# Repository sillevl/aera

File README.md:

# aera
Solar Powered Airquality Station using LoRaWAN

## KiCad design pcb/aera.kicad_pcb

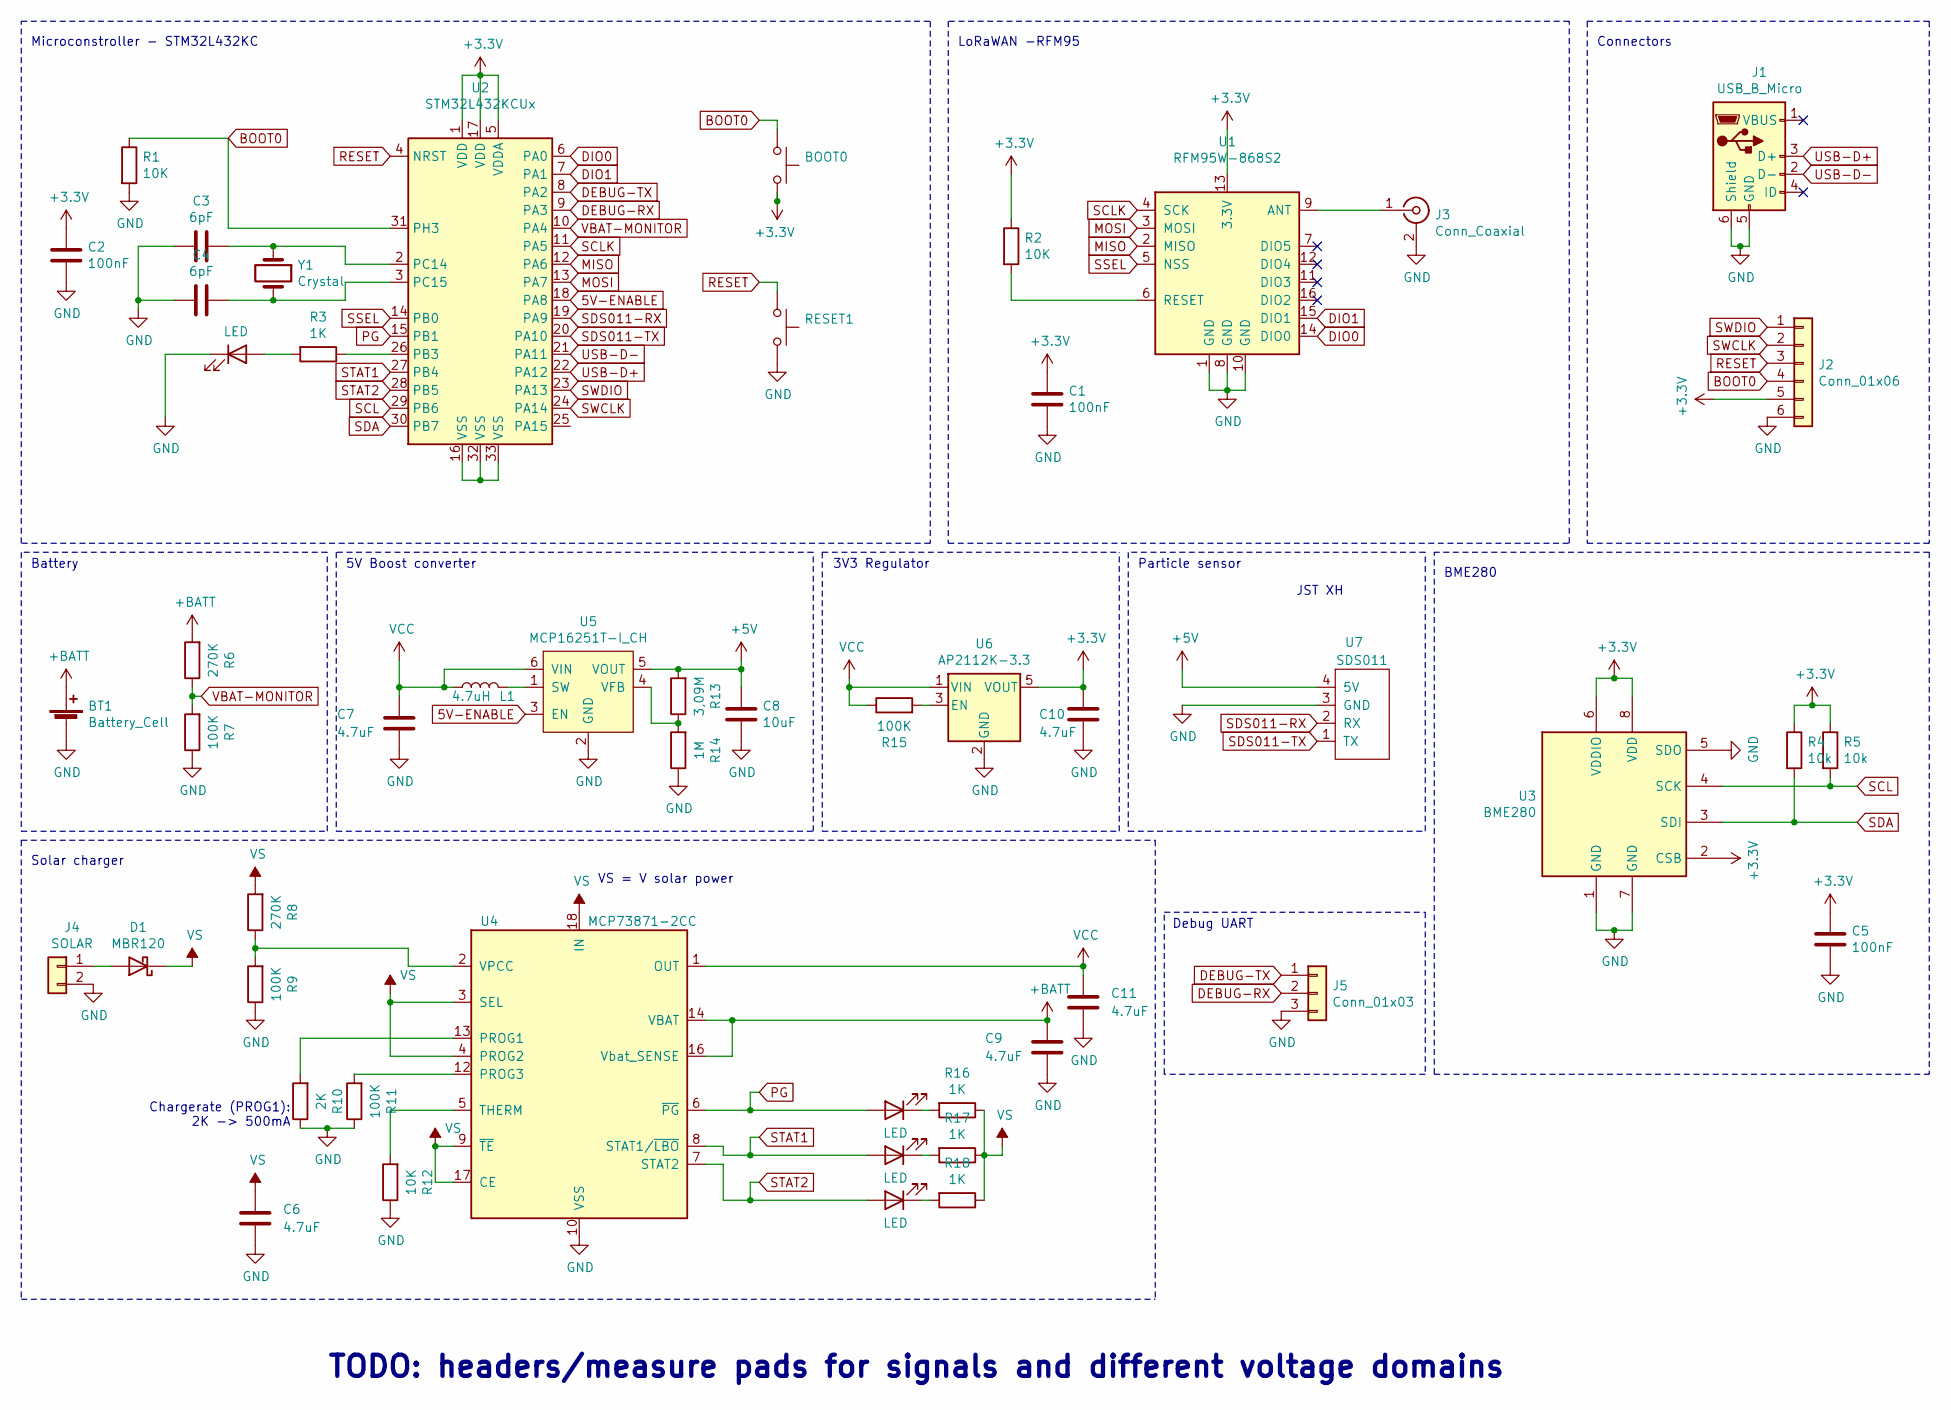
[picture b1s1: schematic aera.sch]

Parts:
BOOT0: BOOT0; SW_SPST_B3U-1000P
BT1: Battery_Cell; BatteryHolder_Keystone_1042_1x18650
C1, C2, C5: 100nF; C_0603_1608Metric_Pad1.05x0.95mm_HandSolder
C3, C4: 6pF; C_0603_1608Metric_Pad1.05x0.95mm_HandSolder
C6, C7, C9, C10, C11: 4.7uF; C_0603_1608Metric_Pad1.05x0.95mm_HandSolder
C8: 10uF; C_0603_1608Metric_Pad1.05x0.95mm_HandSolder
D1: MBR120; D_SOD-123
J1: USB_B_Micro; USB_Micro-AB_Molex_47590-0001
J2: Conn_01x06; PinHeader_1x06_P2.54mm_Vertical
J3: Conn_Coaxial; SMA_Molex_73251-1153_EdgeMount_Horizontal
J4: SOLAR; JST_PH_B2B-PH-SM4-TB_1x02-1MP_P2.00mm_Vertical
J5: Conn_01x03; PinHeader_1x03_P2.54mm_Vertical
L1: 4.7uH; C_0603_1608Metric_Pad1.05x0.95mm_HandSolder
LED1, LED2, LED3, LED4: LED; LED_0603_1608Metric_Pad1.05x0.95mm_HandSolder
R1, R2, R12: 10K; C_0603_1608Metric_Pad1.05x0.95mm_HandSolder
R3, R16, R17, R18: 1K; C_0603_1608Metric_Pad1.05x0.95mm_HandSolder
R4, R5: 10k; C_0603_1608Metric_Pad1.05x0.95mm_HandSolder
R6, R8: 270K; C_0603_1608Metric_Pad1.05x0.95mm_HandSolder
R7, R9, R11, R15: 100K; C_0603_1608Metric_Pad1.05x0.95mm_HandSolder
R10: 2K; C_0603_1608Metric_Pad1.05x0.95mm_HandSolder
R13: 3,09M; C_0603_1608Metric_Pad1.05x0.95mm_HandSolder
R14: 1M; C_0603_1608Metric_Pad1.05x0.95mm_HandSolder
RESET1: RESET; SW_SPST_B3U-1000P
U1: RFM95W-868S2; HOPERF_RFM9XW_SMD
U2: STM32L432KCUx; QFN-32-1EP_5x5mm_P0.5mm_EP3.45x3.45mm
U3: BME280; Bosch_LGA-8_2.5x2.5mm_P0.65mm_ClockwisePinNumbering
U4: MCP73871-2CC; QFN-20-1EP_4x4mm_P0.5mm_EP2.5x2.5mm
U5: MCP16251T-I_CH; SOT-23-6
U6: AP2112K-3.3; TSOT-23-5
U7: SDS011; JST_XH_B5B-XH-A_1x05_P2.50mm_Vertical
Y1: Crystal; Crystal_SMD_Abracon_ABM7-2Pin_6.0x3.5mm

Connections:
5V-ENABLE: U2.18 (PA8), U5.3 (EN)
+3V3: BOOT0.2, C1.1, C2.1, C5.1, C10.1, J2.5, R2.1, R4.1, R5.1, U1.13 (3.3V), U2.1 (VDD), U2.5 (VDDA), U2.17 (VDD), U3.2 (CSB), U3.6 (VDDIO), U3.8 (VDD), U6.5 (VOUT)
+5V: C8.1, R13.2, U5.5 (VOUT), U7.4 (5V)
+BATT: BT1.1 (+), C9.1, R6.2, U4.14 (VBAT), U4.15 (VBAT), U4.16 (Vbat_SENSE)
BOOT0: BOOT0.1, J2.4, R1.1, U2.31 (PH3)
DEBUG-RX: J5.2, U2.9 (PA3)
DEBUG-TX: J5.1, U2.8 (PA2)
DIO0: U1.14 (DIO0), U2.6 (PA0)
DIO1: U1.15 (DIO1), U2.7 (PA1)
GND: BT1.2 (-), C1.2, C2.2, C3.2, C4.2, C5.2, C6.2, C7.2, C8.2, C9.2, C10.2, C11.2, J1.5 (GND), J1.6 (Shield), J2.6, J3.2 (Ext), J4.2, J5.3, LED1.1 (K), R1.2, R7.1, R9.1, R10.1, R11.1, R12.1, R14.1, RESET1.2, U1.1 (GND), U1.8 (GND), U1.10 (GND), U3.1 (GND), U3.5 (SDO), U3.7 (GND), U4.10 (VSS), U4.11 (VSS), U4.21 (VSS), U5.2 (GND), U6.2 (GND), U7.3 (GND)
MISO: U1.2 (MISO), U2.12 (PA6)
MOSI: U1.3 (MOSI), U2.13 (PA7)
unnamed: C3.1, U2.2 (PC14), Y1.1
unnamed: C4.1, U2.3 (PC15), Y1.2
unnamed: D1.2 (A), J4.1
unnamed: J3.1 (In), U1.9 (ANT)
unnamed: L1.2, U5.1 (SW)
unnamed: LED1.2 (A), R3.2
unnamed: LED2.1 (K), R16.2
unnamed: LED3.1 (K), R17.2
unnamed: LED4.1 (K), R18.2
unnamed: R2.2, U1.6 (RESET)
unnamed: R3.1, U2.26 (PB3)
unnamed: R8.1, R9.2, U4.2 (VPCC)
unnamed: R10.2, U4.13 (PROG1)
unnamed: R11.2, U4.12 (PROG3)
unnamed: R12.2, U4.5 (THERM)
unnamed: R13.1, R14.2, U5.4 (VFB)
unnamed: R15.2, U6.3 (EN)
unnamed: U2.16 (VSS), U2.32 (VSS), U2.33 (VSS)
PG: LED2.2 (A), U2.15 (PB1), U4.6 (~PG~)
RESET: J2.3, RESET1.1, U2.4 (NRST)
SCL: R5.2, U2.29 (PB6), U3.4 (SCK)
SCLK: U1.4 (SCK), U2.11 (PA5)
SDA: R4.2, U2.30 (PB7), U3.3 (SDI)
SDS011-RX: U2.19 (PA9), U7.2 (RX)
SDS011-TX: U2.20 (PA10), U7.1 (TX)
SSEL: U1.5 (NSS), U2.14 (PB0)
STAT1: LED3.2 (A), U2.27 (PB4), U4.8 (STAT1/~LBO~)
STAT2: LED4.2 (A), U2.28 (PB5), U4.7 (STAT2)
SWCLK: J2.2, U2.24 (PA14)
SWDIO: J2.1, U2.23 (PA13)
USB-D+: J1.3 (D+), U2.22 (PA12)
USB-D-: J1.2 (D-), U2.21 (PA11)
VBAT-MONITOR: R6.1, R7.2, U2.10 (PA4)
VCC: C7.1, C11.1, L1.1, R15.1, U4.1 (OUT), U4.20 (OUT), U5.6 (VIN), U6.1 (VIN)
VS: C6.1, D1.1 (K), R8.2, R16.1, R17.1, R18.1, U4.3 (SEL), U4.4 (PROG2), U4.9 (~TE), U4.17 (CE), U4.18 (IN), U4.19 (IN)

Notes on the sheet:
BME280
Connectors
LoRaWAN -RFM95
Microconstroller - STM32L432KC
5V Boost converter
Battery
Particle sensor
Solar charger
Debug UART
3V3 Regulator
VS = V solar power
Chargerate (PROG1): 2K -> 500mA
JST XH
TODO: headers/measure pads for signals and different voltage domains

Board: 2 copper layers, 51 parts (0 on the bottom side), 47 nets, no tracks yet.

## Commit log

2020-10-09 first part of schematic
2020-10-10 update schematic
